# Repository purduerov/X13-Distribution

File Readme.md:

# Readme for X13-Distribution

Whenever you make a new part, download the datasheet and save it here _**and**_ with the part in the parts library

Always pull other people's changes before beginning to work
`git pull`

Be sure to push your changes after  working on them. Run:
1. `git add .` to add any files in this directory or a subdirectory
or `git add -u` to add any modified files
2. (Optional) `git clean -nX` to see what ignored files can be removed
	`git clean -fX` removes ignored files (Eagle backups)
3. `git commit -m "helpful commit message"` with a description of the work that you did
4. `git push` to push your work to github

Other helpful commands
* `git status` says information about modified and staged files
* `git log` shows the recent commits of the repository
* `git log filename.extension` show the recent commits for just that file
* `git checkout first-couple-letter-of-commit-id` lets you go back to a previous version
* `git checkout master` brings you back to the latest commit
* `git tag` lists the tags
* `git tag -a orderX -m "the version of the board placed for the X'th order"` tag a specific commit
* `git push --tags` needed to push tags to remote
* `git show orderX` show the commit log for the given tag
* `git checkout orderX` go back and interact with the files at the tagged commit

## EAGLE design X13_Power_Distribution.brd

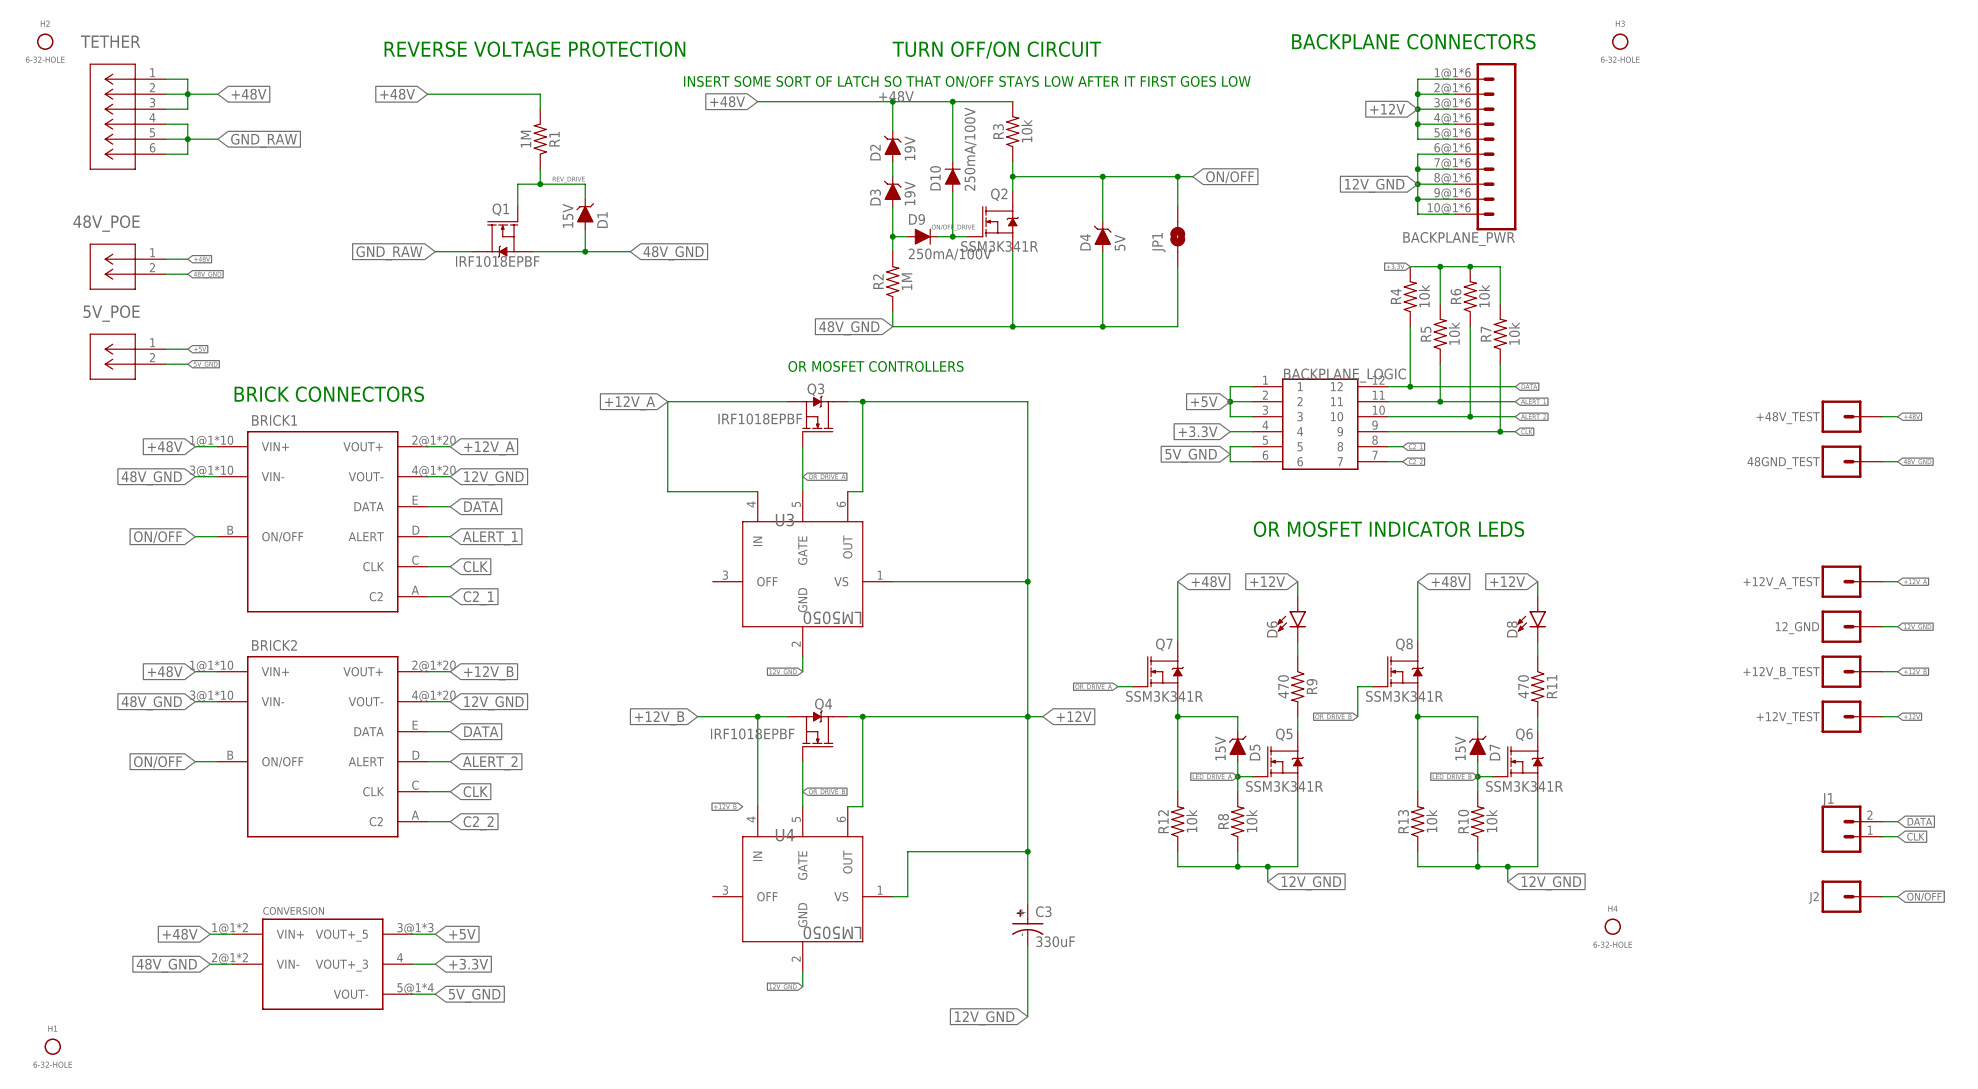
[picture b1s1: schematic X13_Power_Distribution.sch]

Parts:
5V_POE, 48V_POE: POE_TERMINAL; CONN2_282834-2_TEC
12_GND, 48GND_TEST: CONN_01; 1X01
+12V_A_TEST, +12V_B_TEST, +12V_TEST, +48V_TEST: CONN_01; 1X01
BACKPLANE_LOGIC: IPL1-106-01-L-D-K
BACKPLANE_PWR: MPPT-10-01-01-L-RA-SD
BRICK1, BRICK2: DIST2BRICKVER_D2; DIST2BRICK_D2
C3: 330uF; CAPAE1030X1050N
CONVERSION: DIST2CON
D1, D5, D7: 15V; SOD-323
D2, D3: 19V; SOD-323
D4: 5V; SOD-323
D6, D8: LED0603; LED-0603
D9, D10: 250mA/100V; SOD-323
H1, H2, H3, H4: 6-32-HOLE
J1: CONN_02; 1X02
J2: CONN_01; 1X01
JP1: JUMPER-SMT_2_NO_SILK; SMT-JUMPER_2_NO_SILK
Q1, Q3, Q4: IRF1018EPBF; TO263
Q2, Q5, Q6, Q7, Q8: SSM3K341R; SOT323
R1, R2: 1M; 0603
R3, R4, R5, R6, R7, R8, R10, R12, R13: 10k; 0603
R9, R11: 470; 0603
TETHER: 48V; CON6_P5MM_VER_TERM-BLK_TYC
U3, U4: LM5050; SOT-23-6

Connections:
5V_GND: 5V_POE.2, BACKPLANE_LOGIC.5, BACKPLANE_LOGIC.6, CONVERSION.5@1 (VOUT-), CONVERSION.5@2 (VOUT-), CONVERSION.5@3 (VOUT-), CONVERSION.5@4 (VOUT-)
12V_GND: 12_GND.1, BACKPLANE_PWR.6@1 (6), BACKPLANE_PWR.6@2 (6), BACKPLANE_PWR.6@3 (6), BACKPLANE_PWR.6@4 (6), BACKPLANE_PWR.6@5 (6), BACKPLANE_PWR.6@6 (6), BACKPLANE_PWR.7@1 (7), BACKPLANE_PWR.7@2 (7), BACKPLANE_PWR.7@3 (7), BACKPLANE_PWR.7@4 (7), BACKPLANE_PWR.7@5 (7), BACKPLANE_PWR.7@6 (7), BACKPLANE_PWR.8@1 (8), BACKPLANE_PWR.8@2 (8), BACKPLANE_PWR.8@3 (8), BACKPLANE_PWR.8@4 (8), BACKPLANE_PWR.8@5 (8), BACKPLANE_PWR.8@6 (8), BACKPLANE_PWR.9@1 (9), BACKPLANE_PWR.9@2 (9), BACKPLANE_PWR.9@3 (9), BACKPLANE_PWR.9@4 (9), BACKPLANE_PWR.9@5 (9), BACKPLANE_PWR.9@6 (9), BACKPLANE_PWR.10@1 (10), BACKPLANE_PWR.10@2 (10), BACKPLANE_PWR.10@3 (10), BACKPLANE_PWR.10@4 (10), BACKPLANE_PWR.10@5 (10), BACKPLANE_PWR.10@6 (10), BRICK1.4@1 (VOUT-), BRICK1.4@2 (VOUT-), BRICK1.4@3 (VOUT-), BRICK1.4@4 (VOUT-), BRICK1.4@5 (VOUT-), BRICK1.4@6 (VOUT-), BRICK1.4@7 (VOUT-), BRICK1.4@8 (VOUT-), BRICK1.4@9 (VOUT-), BRICK1.4@10 (VOUT-), BRICK1.4@11 (VOUT-), BRICK1.4@12 (VOUT-), BRICK1.4@13 (VOUT-), BRICK1.4@14 (VOUT-), BRICK1.4@15 (VOUT-), BRICK1.4@16 (VOUT-), BRICK1.4@17 (VOUT-), BRICK1.4@18 (VOUT-), BRICK1.4@19 (VOUT-), BRICK1.4@20 (VOUT-), BRICK2.4@1 (VOUT-), BRICK2.4@2 (VOUT-), BRICK2.4@3 (VOUT-), BRICK2.4@4 (VOUT-), BRICK2.4@5 (VOUT-), BRICK2.4@6 (VOUT-), BRICK2.4@7 (VOUT-), BRICK2.4@8 (VOUT-), BRICK2.4@9 (VOUT-), BRICK2.4@10 (VOUT-), BRICK2.4@11 (VOUT-), BRICK2.4@12 (VOUT-), BRICK2.4@13 (VOUT-), BRICK2.4@14 (VOUT-), BRICK2.4@15 (VOUT-), BRICK2.4@16 (VOUT-), BRICK2.4@17 (VOUT-), BRICK2.4@18 (VOUT-), BRICK2.4@19 (VOUT-), BRICK2.4@20 (VOUT-), C3.-, Q5.2 (S), Q6.2 (S), R8.1, R10.1, R12.1, R13.1, U3.2 (GND), U4.2 (GND)
48V_GND: 48GND_TEST.1, 48V_POE.2, BRICK1.3@1 (VIN-), BRICK1.3@2 (VIN-), BRICK1.3@3 (VIN-), BRICK1.3@4 (VIN-), BRICK1.3@5 (VIN-), BRICK1.3@6 (VIN-), BRICK1.3@7 (VIN-), BRICK1.3@8 (VIN-), BRICK1.3@9 (VIN-), BRICK1.3@10 (VIN-), BRICK2.3@1 (VIN-), BRICK2.3@2 (VIN-), BRICK2.3@3 (VIN-), BRICK2.3@4 (VIN-), BRICK2.3@5 (VIN-), BRICK2.3@6 (VIN-), BRICK2.3@7 (VIN-), BRICK2.3@8 (VIN-), BRICK2.3@9 (VIN-), BRICK2.3@10 (VIN-), CONVERSION.2@1 (VIN-), CONVERSION.2@2 (VIN-), D1.A, D4.A, JP1.1, Q1.2 (S), Q2.2 (S), R2.1
+3.3V: BACKPLANE_LOGIC.4, CONVERSION.4 (VOUT+_3), R4.2, R5.2, R6.2, R7.2
+5V: 5V_POE.1, BACKPLANE_LOGIC.1, BACKPLANE_LOGIC.2, BACKPLANE_LOGIC.3, CONVERSION.3@1 (VOUT+_5), CONVERSION.3@2 (VOUT+_5), CONVERSION.3@3 (VOUT+_5)
+12V: +12V_TEST.1, BACKPLANE_PWR.1@1 (1), BACKPLANE_PWR.1@2 (1), BACKPLANE_PWR.1@3 (1), BACKPLANE_PWR.1@4 (1), BACKPLANE_PWR.1@5 (1), BACKPLANE_PWR.1@6 (1), BACKPLANE_PWR.2@1 (2), BACKPLANE_PWR.2@2 (2), BACKPLANE_PWR.2@3 (2), BACKPLANE_PWR.2@4 (2), BACKPLANE_PWR.2@5 (2), BACKPLANE_PWR.2@6 (2), BACKPLANE_PWR.3@1 (3), BACKPLANE_PWR.3@2 (3), BACKPLANE_PWR.3@3 (3), BACKPLANE_PWR.3@4 (3), BACKPLANE_PWR.3@5 (3), BACKPLANE_PWR.3@6 (3), BACKPLANE_PWR.4@1 (4), BACKPLANE_PWR.4@2 (4), BACKPLANE_PWR.4@3 (4), BACKPLANE_PWR.4@4 (4), BACKPLANE_PWR.4@5 (4), BACKPLANE_PWR.4@6 (4), BACKPLANE_PWR.5@1 (5), BACKPLANE_PWR.5@2 (5), BACKPLANE_PWR.5@3 (5), BACKPLANE_PWR.5@4 (5), BACKPLANE_PWR.5@5 (5), BACKPLANE_PWR.5@6 (5), C3.+, D6.A, D8.A, Q3.3 (D), Q4.3 (D), U3.1 (VS), U3.6 (OUT), U4.1 (VS), U4.6 (OUT)
+12V_A: +12V_A_TEST.1, BRICK1.2@1 (VOUT+), BRICK1.2@2 (VOUT+), BRICK1.2@3 (VOUT+), BRICK1.2@4 (VOUT+), BRICK1.2@5 (VOUT+), BRICK1.2@6 (VOUT+), BRICK1.2@7 (VOUT+), BRICK1.2@8 (VOUT+), BRICK1.2@9 (VOUT+), BRICK1.2@10 (VOUT+), BRICK1.2@11 (VOUT+), BRICK1.2@12 (VOUT+), BRICK1.2@13 (VOUT+), BRICK1.2@14 (VOUT+), BRICK1.2@15 (VOUT+), BRICK1.2@16 (VOUT+), BRICK1.2@17 (VOUT+), BRICK1.2@18 (VOUT+), BRICK1.2@19 (VOUT+), BRICK1.2@20 (VOUT+), Q3.2 (S), U3.4 (IN)
+12V_B: +12V_B_TEST.1, BRICK2.2@1 (VOUT+), BRICK2.2@2 (VOUT+), BRICK2.2@3 (VOUT+), BRICK2.2@4 (VOUT+), BRICK2.2@5 (VOUT+), BRICK2.2@6 (VOUT+), BRICK2.2@7 (VOUT+), BRICK2.2@8 (VOUT+), BRICK2.2@9 (VOUT+), BRICK2.2@10 (VOUT+), BRICK2.2@11 (VOUT+), BRICK2.2@12 (VOUT+), BRICK2.2@13 (VOUT+), BRICK2.2@14 (VOUT+), BRICK2.2@15 (VOUT+), BRICK2.2@16 (VOUT+), BRICK2.2@17 (VOUT+), BRICK2.2@18 (VOUT+), BRICK2.2@19 (VOUT+), BRICK2.2@20 (VOUT+), Q4.2 (S), U4.4 (IN)
+48V: 48V_POE.1, +48V_TEST.1, BRICK1.1@1 (VIN+), BRICK1.1@2 (VIN+), BRICK1.1@3 (VIN+), BRICK1.1@4 (VIN+), BRICK1.1@5 (VIN+), BRICK1.1@6 (VIN+), BRICK1.1@7 (VIN+), BRICK1.1@8 (VIN+), BRICK1.1@9 (VIN+), BRICK1.1@10 (VIN+), BRICK2.1@1 (VIN+), BRICK2.1@2 (VIN+), BRICK2.1@3 (VIN+), BRICK2.1@4 (VIN+), BRICK2.1@5 (VIN+), BRICK2.1@6 (VIN+), BRICK2.1@7 (VIN+), BRICK2.1@8 (VIN+), BRICK2.1@9 (VIN+), BRICK2.1@10 (VIN+), CONVERSION.1@1 (VIN+), CONVERSION.1@2 (VIN+), D2.C, D10.C, Q7.3 (D), Q8.3 (D), R1.2, R3.2, TETHER.1, TETHER.2, TETHER.3
ALERT_1: BACKPLANE_LOGIC.11, BRICK1.D (ALERT), R5.1
ALERT_2: BACKPLANE_LOGIC.10, BRICK2.D (ALERT), R6.1
C2_1: BACKPLANE_LOGIC.8, BRICK1.A (C2)
C2_2: BACKPLANE_LOGIC.7, BRICK2.A (C2)
CLK: BACKPLANE_LOGIC.9, BRICK1.C (CLK), BRICK2.C (CLK), J1.1, R7.1
DATA: BACKPLANE_LOGIC.12, BRICK1.E (DATA), BRICK2.E (DATA), J1.2, R4.1
GND_RAW: Q1.3 (D), TETHER.4, TETHER.5, TETHER.6
LED_DRIVE_A: D5.A, Q5.1 (G), R8.2
LED_DRIVE_B: D7.A, Q6.1 (G), R10.2
unnamed: D2.A, D3.C
unnamed: D5.C, Q7.2 (S), R12.2
unnamed: D7.C, Q8.2 (S), R13.2
unnamed: Q5.3 (D), R9.2
unnamed: D6.C, R9.1
unnamed: Q6.3 (D), R11.2
unnamed: D8.C, R11.1
ON/OFF: BRICK1.B (ON/OFF), BRICK2.B (ON/OFF), D4.C, J2.1, JP1.2, Q2.3 (D), R3.1
ON/OFF_DRIVE: D9.C, D10.A, Q2.1 (G)
ON_DETECT: D3.A, D9.A, R2.2
OR_DRIVE_A: Q3.1 (G), Q7.1 (G), U3.5 (GATE)
OR_DRIVE_B: Q4.1 (G), Q8.1 (G), U4.5 (GATE)
REV_DRIVE: D1.C, Q1.1 (G), R1.1

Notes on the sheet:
TURN OFF/ON CIRCUIT
REVERSE VOLTAGE PROTECTION
OR MOSFET CONTROLLERS
OR MOSFET INDICATOR LEDS
BACKPLANE CONNECTORS
BRICK CONNECTORS
INSERT SOME SORT OF LATCH SO THAT ON/OFF STAYS LOW AFTER IT FIRST GOES LOW

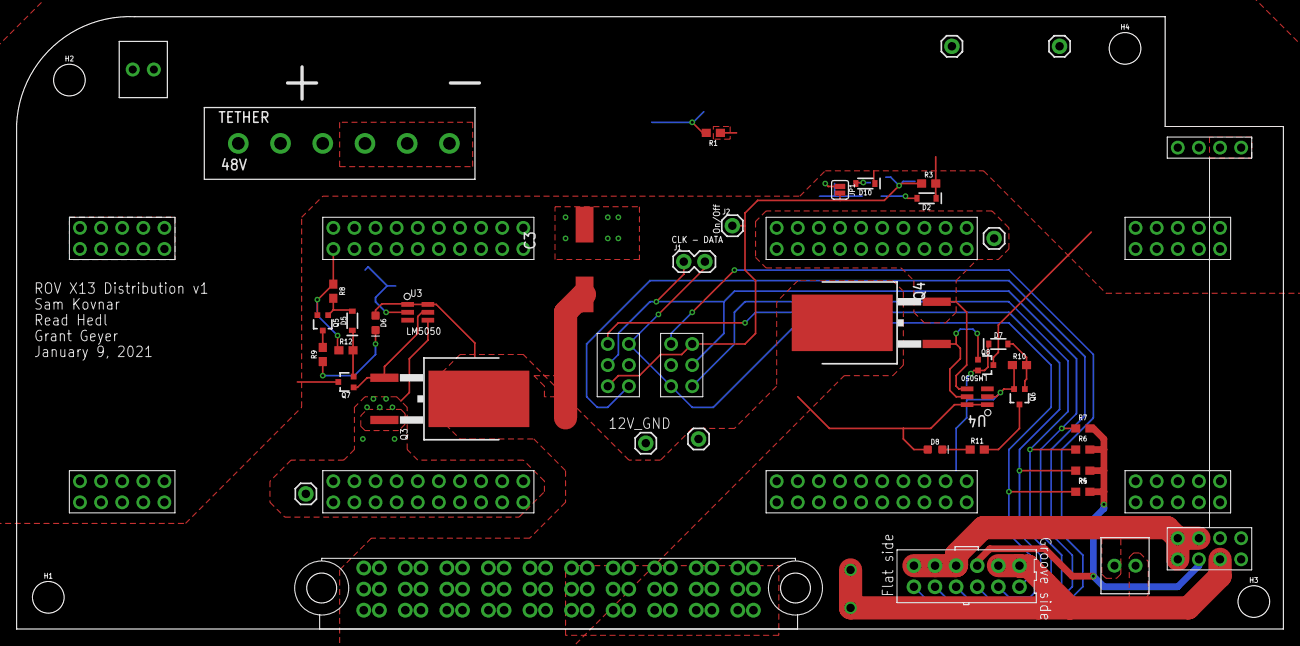
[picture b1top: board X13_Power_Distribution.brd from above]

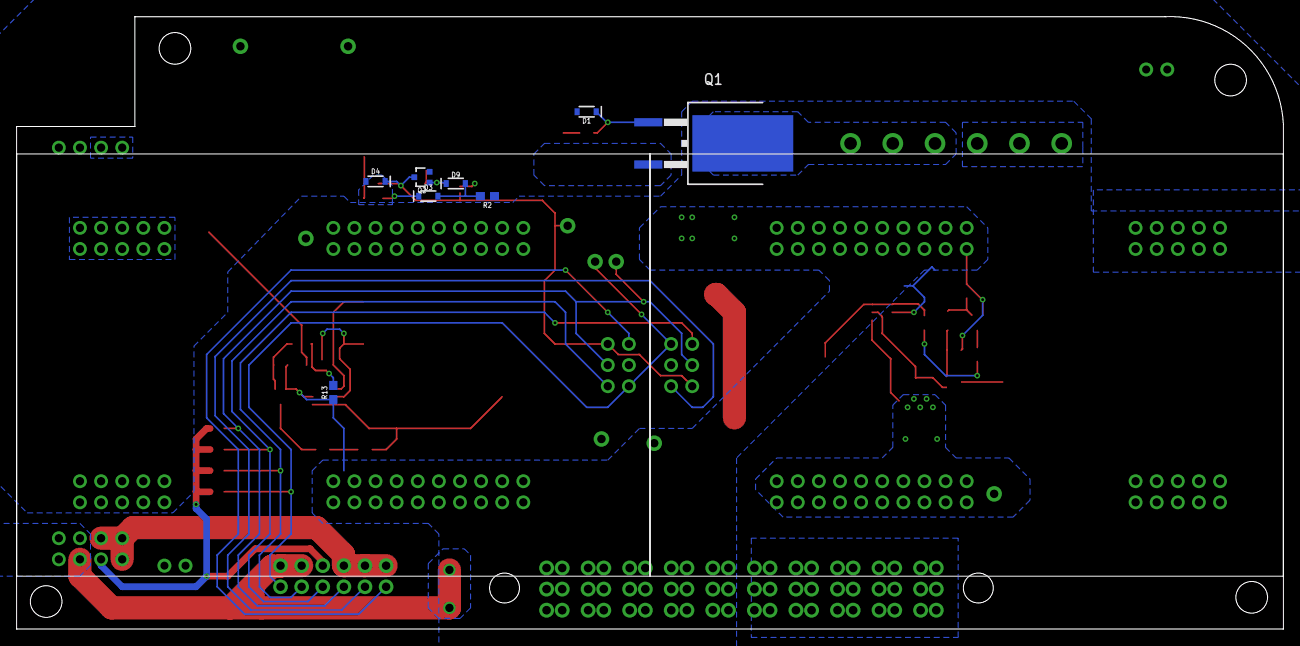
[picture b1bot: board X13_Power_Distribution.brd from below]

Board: 2 copper layers, 152.4 x 73.7 mm, 55 parts (8 on the bottom side), 31 nets.

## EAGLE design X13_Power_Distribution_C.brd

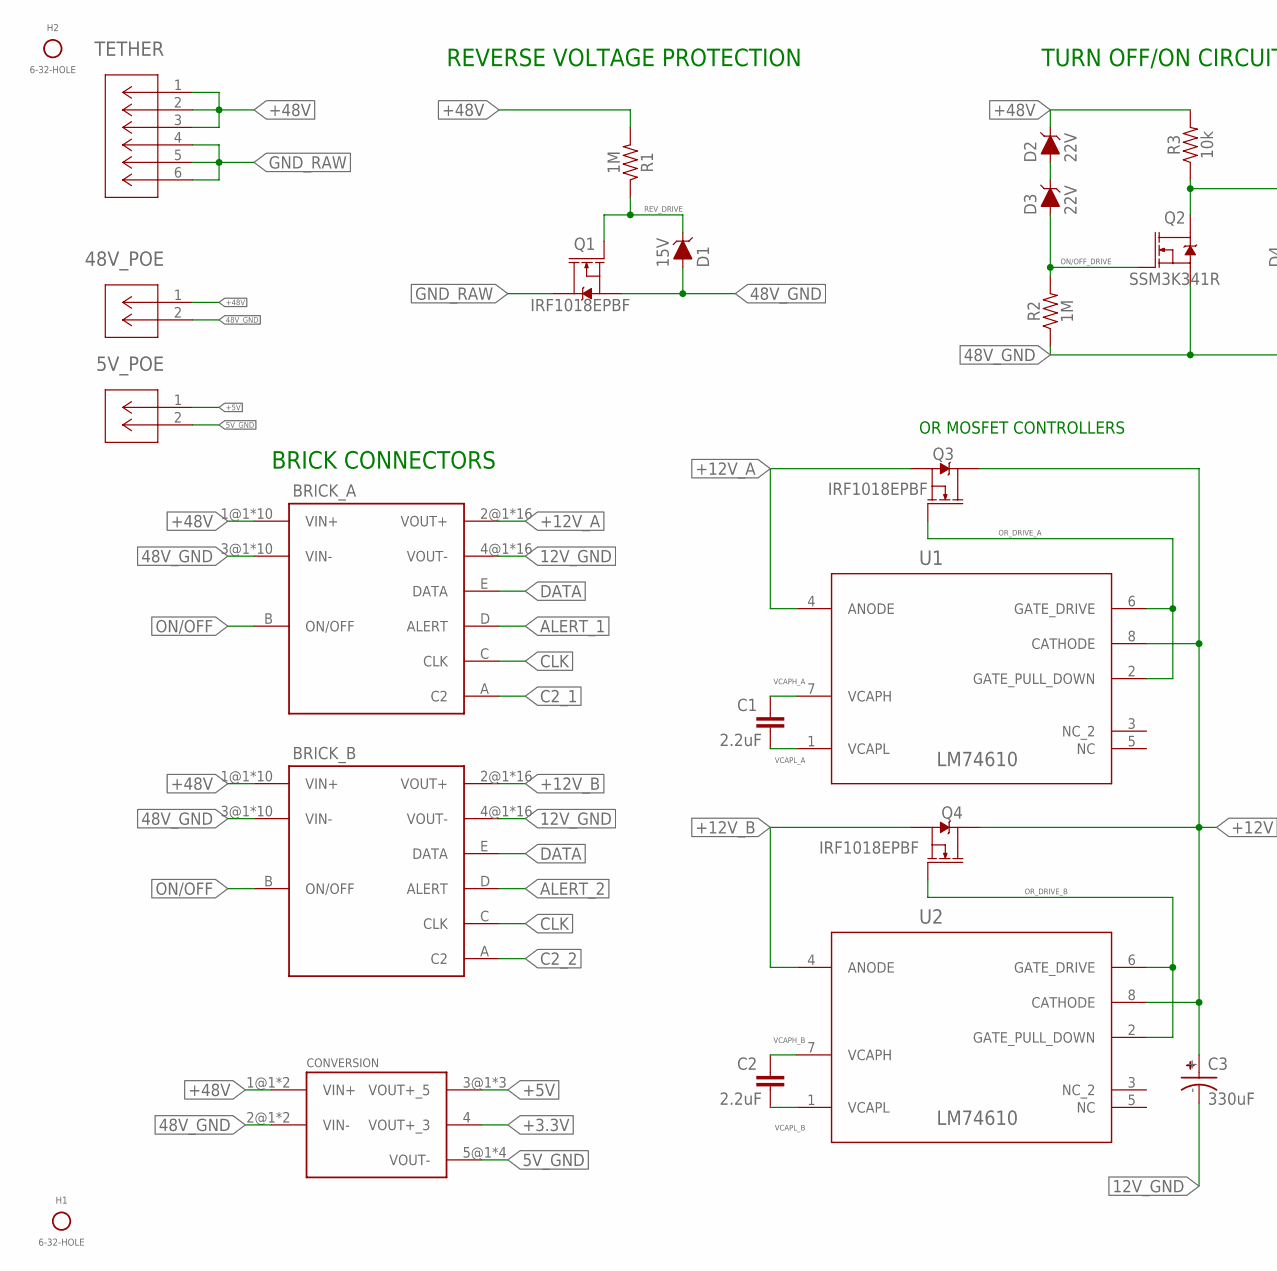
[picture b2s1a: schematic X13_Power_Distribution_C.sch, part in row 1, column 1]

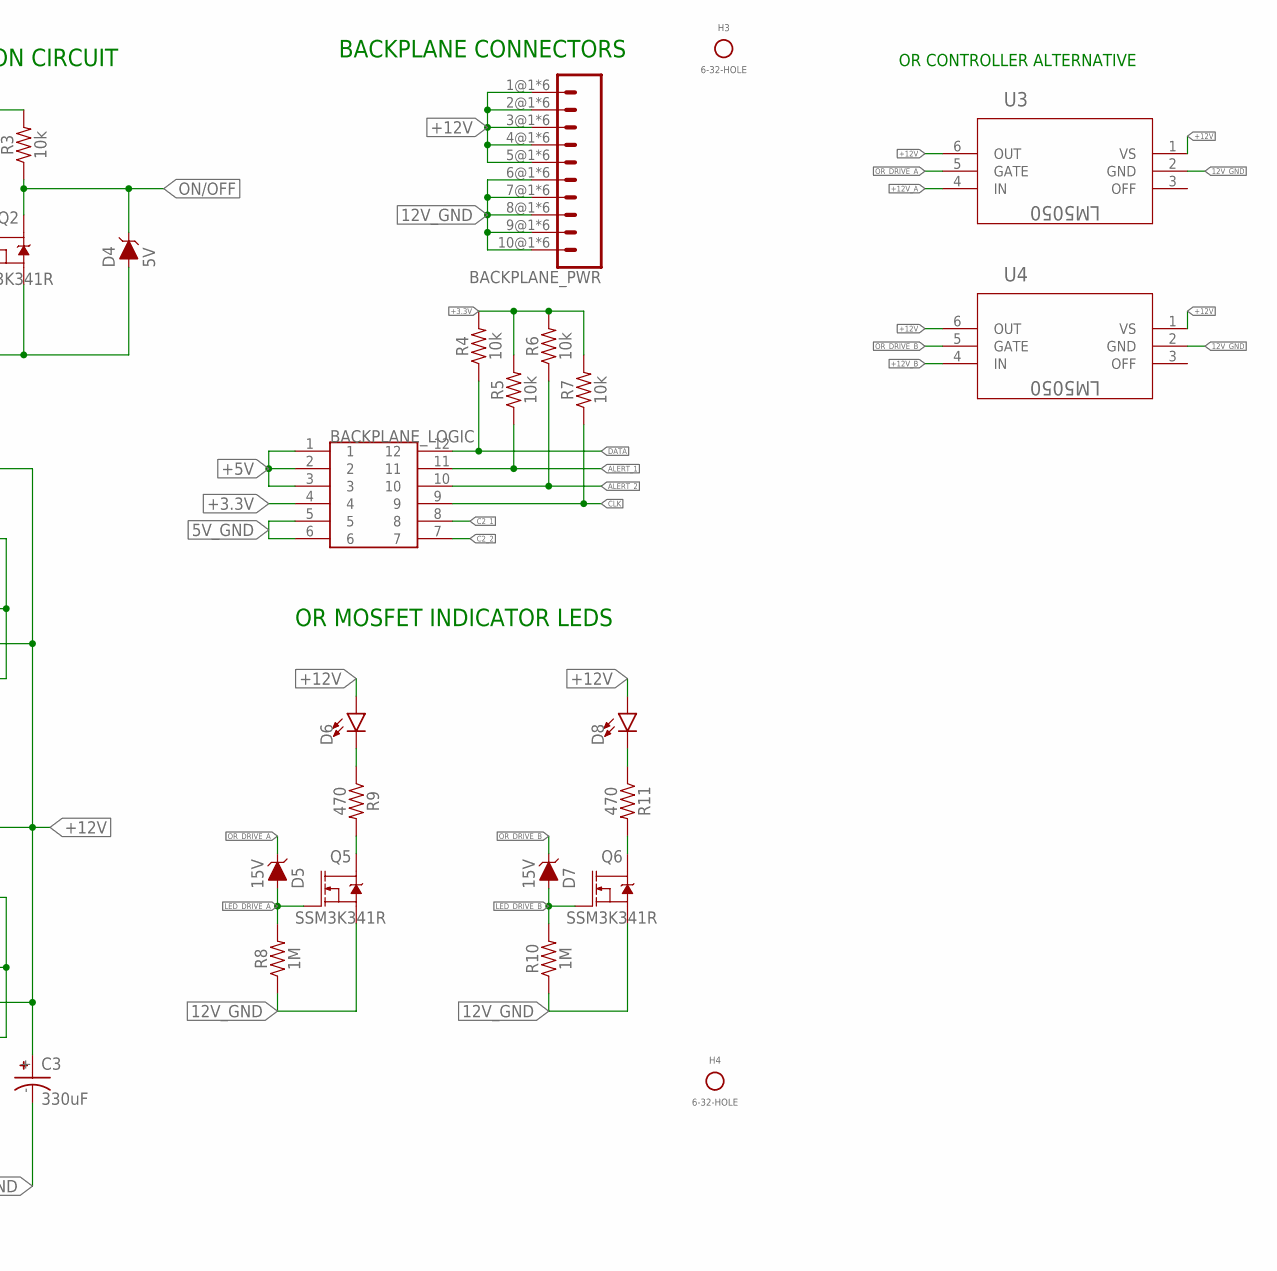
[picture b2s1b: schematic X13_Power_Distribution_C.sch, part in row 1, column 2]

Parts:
5V_POE, 48V_POE: POE_TERMINAL; CONN2_282834-2_TEC
BACKPLANE_LOGIC: IPL1-106-01-L-D-RE1-K
BACKPLANE_PWR: MPPT-10-01-01-L-RA-SD
BRICK_A: DIST2BRICK_C
BRICK_B: DIST2BRICK_C
C1, C2: 2.2uF; 0603
C3: 330uF; CAPAE1030X1050N
CONVERSION: DIST2CON
D1, D5, D7: 15V; SOD-323
D2, D3: 22V; SOD-323
D4: 5V; SOD-323
D6, D8: LED0603; LED-0603
H1, H2, H3, H4: 6-32-HOLE
Q1, Q3, Q4: IRF1018EPBF; TO263
Q2, Q5, Q6: SSM3K341R; SOT323
R1, R2, R8, R10: 1M; 0603
R3, R4, R5, R6, R7: 10k; 0603
R9, R11: 470; 0603
TETHER: 48V; CON6_P5MM_VER_TERM-BLK_TYC
U1, U2: LM74610; DGK0008A_M
U3, U4: LM5050; MK06A-M

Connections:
5V_GND: 5V_POE.2, BACKPLANE_LOGIC.5, BACKPLANE_LOGIC.6, CONVERSION.5@1 (VOUT-), CONVERSION.5@2 (VOUT-), CONVERSION.5@3 (VOUT-), CONVERSION.5@4 (VOUT-)
12V_GND: BACKPLANE_PWR.6@1 (6), BACKPLANE_PWR.6@2 (6), BACKPLANE_PWR.6@3 (6), BACKPLANE_PWR.6@4 (6), BACKPLANE_PWR.6@5 (6), BACKPLANE_PWR.6@6 (6), BACKPLANE_PWR.7@1 (7), BACKPLANE_PWR.7@2 (7), BACKPLANE_PWR.7@3 (7), BACKPLANE_PWR.7@4 (7), BACKPLANE_PWR.7@5 (7), BACKPLANE_PWR.7@6 (7), BACKPLANE_PWR.8@1 (8), BACKPLANE_PWR.8@2 (8), BACKPLANE_PWR.8@3 (8), BACKPLANE_PWR.8@4 (8), BACKPLANE_PWR.8@5 (8), BACKPLANE_PWR.8@6 (8), BACKPLANE_PWR.9@1 (9), BACKPLANE_PWR.9@2 (9), BACKPLANE_PWR.9@3 (9), BACKPLANE_PWR.9@4 (9), BACKPLANE_PWR.9@5 (9), BACKPLANE_PWR.9@6 (9), BACKPLANE_PWR.10@1 (10), BACKPLANE_PWR.10@2 (10), BACKPLANE_PWR.10@3 (10), BACKPLANE_PWR.10@4 (10), BACKPLANE_PWR.10@5 (10), BACKPLANE_PWR.10@6 (10), BRICK_A.4@1 (VOUT-), BRICK_A.4@2 (VOUT-), BRICK_A.4@3 (VOUT-), BRICK_A.4@4 (VOUT-), BRICK_A.4@5 (VOUT-), BRICK_A.4@6 (VOUT-), BRICK_A.4@7 (VOUT-), BRICK_A.4@8 (VOUT-), BRICK_A.4@9 (VOUT-), BRICK_A.4@10 (VOUT-), BRICK_A.4@11 (VOUT-), BRICK_A.4@12 (VOUT-), BRICK_A.4@13 (VOUT-), BRICK_A.4@14 (VOUT-), BRICK_A.4@15 (VOUT-), BRICK_A.4@16 (VOUT-), BRICK_B.4@1 (VOUT-), BRICK_B.4@2 (VOUT-), BRICK_B.4@3 (VOUT-), BRICK_B.4@4 (VOUT-), BRICK_B.4@5 (VOUT-), BRICK_B.4@6 (VOUT-), BRICK_B.4@7 (VOUT-), BRICK_B.4@8 (VOUT-), BRICK_B.4@9 (VOUT-), BRICK_B.4@10 (VOUT-), BRICK_B.4@11 (VOUT-), BRICK_B.4@12 (VOUT-), BRICK_B.4@13 (VOUT-), BRICK_B.4@14 (VOUT-), BRICK_B.4@15 (VOUT-), BRICK_B.4@16 (VOUT-), C3.-, Q5.2 (S), Q6.2 (S), R8.1, R10.1, U3.2 (GND), U4.2 (GND)
48V_GND: 48V_POE.2, BRICK_A.3@1 (VIN-), BRICK_A.3@2 (VIN-), BRICK_A.3@3 (VIN-), BRICK_A.3@4 (VIN-), BRICK_A.3@5 (VIN-), BRICK_A.3@6 (VIN-), BRICK_A.3@7 (VIN-), BRICK_A.3@8 (VIN-), BRICK_A.3@9 (VIN-), BRICK_A.3@10 (VIN-), BRICK_B.3@1 (VIN-), BRICK_B.3@2 (VIN-), BRICK_B.3@3 (VIN-), BRICK_B.3@4 (VIN-), BRICK_B.3@5 (VIN-), BRICK_B.3@6 (VIN-), BRICK_B.3@7 (VIN-), BRICK_B.3@8 (VIN-), BRICK_B.3@9 (VIN-), BRICK_B.3@10 (VIN-), CONVERSION.2@1 (VIN-), CONVERSION.2@2 (VIN-), D1.A, D4.A, Q1.2 (S), Q2.2 (S), R2.1
+3.3V: BACKPLANE_LOGIC.4, CONVERSION.4 (VOUT+_3), R4.2, R5.2, R6.2, R7.2
+5V: 5V_POE.1, BACKPLANE_LOGIC.1, BACKPLANE_LOGIC.2, BACKPLANE_LOGIC.3, CONVERSION.3@1 (VOUT+_5), CONVERSION.3@2 (VOUT+_5), CONVERSION.3@3 (VOUT+_5)
+12V: BACKPLANE_PWR.1@1 (1), BACKPLANE_PWR.1@2 (1), BACKPLANE_PWR.1@3 (1), BACKPLANE_PWR.1@4 (1), BACKPLANE_PWR.1@5 (1), BACKPLANE_PWR.1@6 (1), BACKPLANE_PWR.2@1 (2), BACKPLANE_PWR.2@2 (2), BACKPLANE_PWR.2@3 (2), BACKPLANE_PWR.2@4 (2), BACKPLANE_PWR.2@5 (2), BACKPLANE_PWR.2@6 (2), BACKPLANE_PWR.3@1 (3), BACKPLANE_PWR.3@2 (3), BACKPLANE_PWR.3@3 (3), BACKPLANE_PWR.3@4 (3), BACKPLANE_PWR.3@5 (3), BACKPLANE_PWR.3@6 (3), BACKPLANE_PWR.4@1 (4), BACKPLANE_PWR.4@2 (4), BACKPLANE_PWR.4@3 (4), BACKPLANE_PWR.4@4 (4), BACKPLANE_PWR.4@5 (4), BACKPLANE_PWR.4@6 (4), BACKPLANE_PWR.5@1 (5), BACKPLANE_PWR.5@2 (5), BACKPLANE_PWR.5@3 (5), BACKPLANE_PWR.5@4 (5), BACKPLANE_PWR.5@5 (5), BACKPLANE_PWR.5@6 (5), C3.+, D6.A, D8.A, Q3.3 (D), Q4.3 (D), U1.8 (CATHODE), U2.8 (CATHODE), U3.1 (VS), U3.6 (OUT), U4.1 (VS), U4.6 (OUT)
+12V_A: BRICK_A.2@1 (VOUT+), BRICK_A.2@2 (VOUT+), BRICK_A.2@3 (VOUT+), BRICK_A.2@4 (VOUT+), BRICK_A.2@5 (VOUT+), BRICK_A.2@6 (VOUT+), BRICK_A.2@7 (VOUT+), BRICK_A.2@8 (VOUT+), BRICK_A.2@9 (VOUT+), BRICK_A.2@10 (VOUT+), BRICK_A.2@11 (VOUT+), BRICK_A.2@12 (VOUT+), BRICK_A.2@13 (VOUT+), BRICK_A.2@14 (VOUT+), BRICK_A.2@15 (VOUT+), BRICK_A.2@16 (VOUT+), Q3.2 (S), U1.4 (ANODE), U3.4 (IN)
+12V_B: BRICK_B.2@1 (VOUT+), BRICK_B.2@2 (VOUT+), BRICK_B.2@3 (VOUT+), BRICK_B.2@4 (VOUT+), BRICK_B.2@5 (VOUT+), BRICK_B.2@6 (VOUT+), BRICK_B.2@7 (VOUT+), BRICK_B.2@8 (VOUT+), BRICK_B.2@9 (VOUT+), BRICK_B.2@10 (VOUT+), BRICK_B.2@11 (VOUT+), BRICK_B.2@12 (VOUT+), BRICK_B.2@13 (VOUT+), BRICK_B.2@14 (VOUT+), BRICK_B.2@15 (VOUT+), BRICK_B.2@16 (VOUT+), Q4.2 (S), U2.4 (ANODE), U4.4 (IN)
+48V: 48V_POE.1, BRICK_A.1@1 (VIN+), BRICK_A.1@2 (VIN+), BRICK_A.1@3 (VIN+), BRICK_A.1@4 (VIN+), BRICK_A.1@5 (VIN+), BRICK_A.1@6 (VIN+), BRICK_A.1@7 (VIN+), BRICK_A.1@8 (VIN+), BRICK_A.1@9 (VIN+), BRICK_A.1@10 (VIN+), BRICK_B.1@1 (VIN+), BRICK_B.1@2 (VIN+), BRICK_B.1@3 (VIN+), BRICK_B.1@4 (VIN+), BRICK_B.1@5 (VIN+), BRICK_B.1@6 (VIN+), BRICK_B.1@7 (VIN+), BRICK_B.1@8 (VIN+), BRICK_B.1@9 (VIN+), BRICK_B.1@10 (VIN+), CONVERSION.1@1 (VIN+), CONVERSION.1@2 (VIN+), D2.C, R1.2, R3.2, TETHER.1, TETHER.2, TETHER.3
ALERT_1: BACKPLANE_LOGIC.11, BRICK_A.D (ALERT), R5.1
ALERT_2: BACKPLANE_LOGIC.10, BRICK_B.D (ALERT), R6.1
C2_1: BACKPLANE_LOGIC.8, BRICK_A.A (C2)
C2_2: BACKPLANE_LOGIC.7, BRICK_B.A (C2)
CLK: BACKPLANE_LOGIC.9, BRICK_A.C (CLK), BRICK_B.C (CLK), R7.1
DATA: BACKPLANE_LOGIC.12, BRICK_A.E (DATA), BRICK_B.E (DATA), R4.1
GND_RAW: Q1.3 (D), TETHER.4, TETHER.5, TETHER.6
LED_DRIVE_A: D5.A, Q5.1 (G), R8.2
LED_DRIVE_B: D7.A, Q6.1 (G), R10.2
unnamed: D2.A, D3.C
unnamed: Q5.3 (D), R9.2
unnamed: D6.C, R9.1
unnamed: Q6.3 (D), R11.2
unnamed: D8.C, R11.1
ON/OFF: BRICK_A.B (ON/OFF), BRICK_B.B (ON/OFF), D4.C, Q2.3 (D), R3.1
ON/OFF_DRIVE: D3.A, Q2.1 (G), R2.2
OR_DRIVE_A: D5.C, Q3.1 (G), U1.2 (GATE_PULL_DOWN), U1.6 (GATE_DRIVE), U3.5 (GATE)
OR_DRIVE_B: D7.C, Q4.1 (G), U2.2 (GATE_PULL_DOWN), U2.6 (GATE_DRIVE), U4.5 (GATE)
REV_DRIVE: D1.C, Q1.1 (G), R1.1
VCAPH_A: C1.1, U1.7 (VCAPH)
VCAPH_B: C2.1, U2.7 (VCAPH)
VCAPL_A: C1.2, U1.1 (VCAPL)
VCAPL_B: C2.2, U2.1 (VCAPL)

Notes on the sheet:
TURN OFF/ON CIRCUIT
REVERSE VOLTAGE PROTECTION
OR MOSFET CONTROLLERS
OR MOSFET INDICATOR LEDS
BACKPLANE CONNECTORS
BRICK CONNECTORS
OR CONTROLLER ALTERNATIVE

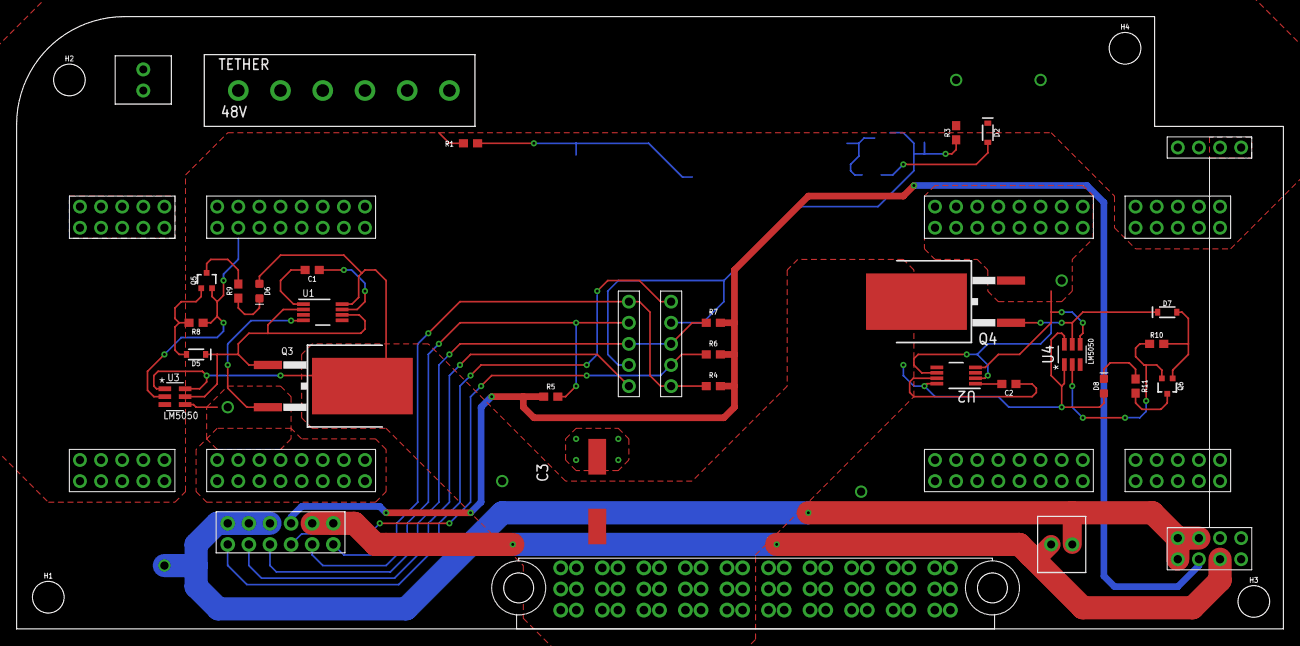
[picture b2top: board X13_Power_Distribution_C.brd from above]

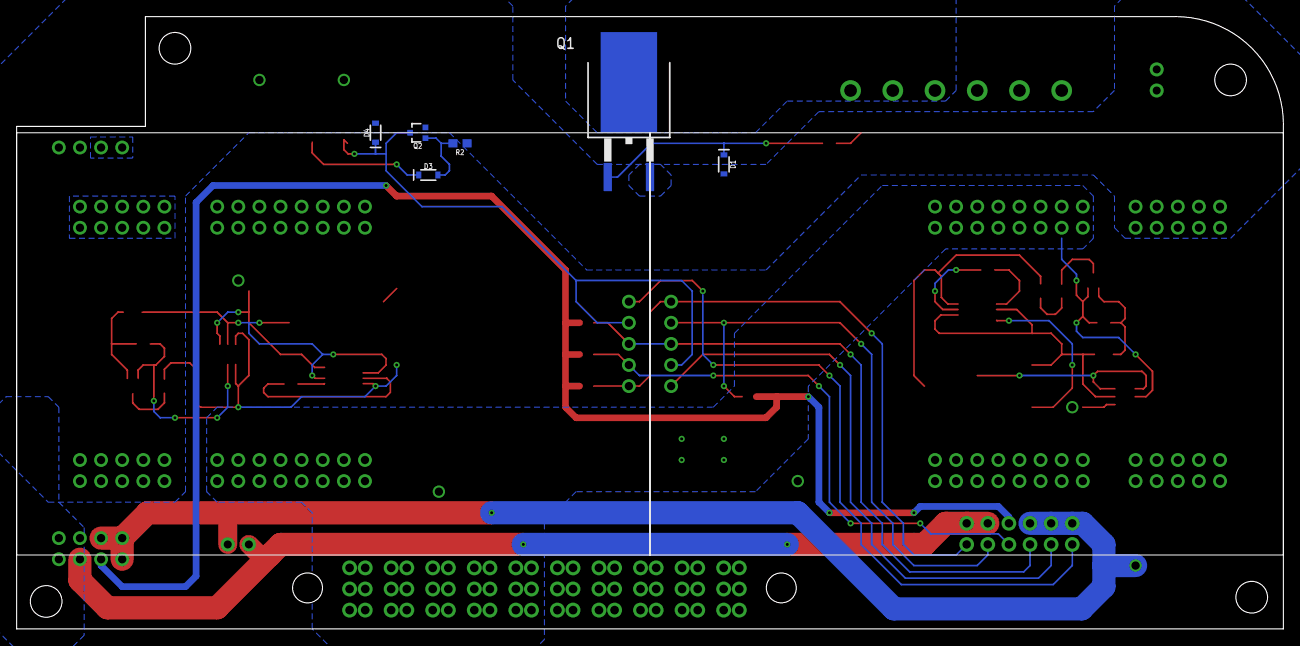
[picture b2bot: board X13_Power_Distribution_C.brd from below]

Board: 2 copper layers, 152.4 x 73.7 mm, 44 parts (6 on the bottom side), 32 nets.

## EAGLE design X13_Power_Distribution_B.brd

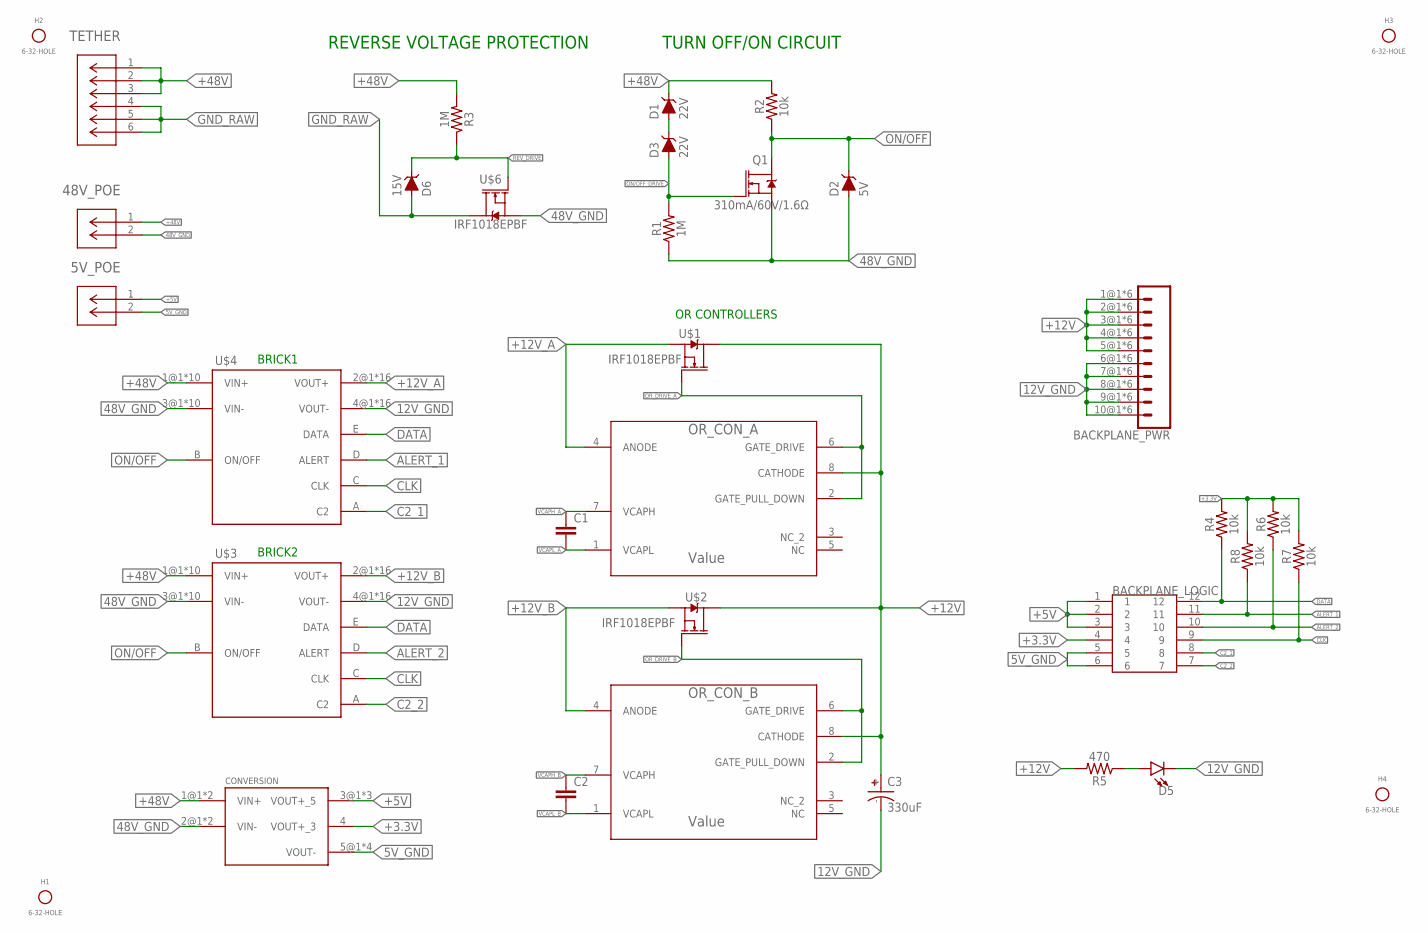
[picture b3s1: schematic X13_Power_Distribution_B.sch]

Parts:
5V_POE, 48V_POE: POE_TERMINAL; CONN2_282834-2_TEC
BACKPLANE_LOGIC: IPL1-107-01-L-D-RE-P
BACKPLANE_PWR: MPPT-10-01-01-L-RA-SD
C1, C2: 0.1UF-0603-100V-10%; 0603
C3: 330uF; CAPAE1030X1050N
CONVERSION: DIST2CON
D1, D3: 22V; SOD-323
D2: 5V; SOD-323
D5: LED0603; LED-0603
D6: 15V; SOD-323
H1, H2, H3, H4: 6-32-HOLE
OR_CON_A: Value; DGK0008A_M
OR_CON_B: Value; DGK0008A_M
Q1: 310mA/60V/1.6Ω; SOT323
R1, R3: 1M; 0603
R2, R4, R6, R7, R8: 10k; 0603
R5: 470; 0603
TETHER: 48V; CON6_P5MM_VER_TERM-BLK_TYC
U$1, U$2, U$6: IRF1018EPBF; TO263
U$3, U$4: DIST2BRICK_B

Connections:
5V_GND: 5V_POE.2, BACKPLANE_LOGIC.5, BACKPLANE_LOGIC.6, CONVERSION.5@1 (VOUT-), CONVERSION.5@2 (VOUT-), CONVERSION.5@3 (VOUT-), CONVERSION.5@4 (VOUT-)
12V_GND: BACKPLANE_PWR.6@1 (6), BACKPLANE_PWR.6@2 (6), BACKPLANE_PWR.6@3 (6), BACKPLANE_PWR.6@4 (6), BACKPLANE_PWR.6@5 (6), BACKPLANE_PWR.6@6 (6), BACKPLANE_PWR.7@1 (7), BACKPLANE_PWR.7@2 (7), BACKPLANE_PWR.7@3 (7), BACKPLANE_PWR.7@4 (7), BACKPLANE_PWR.7@5 (7), BACKPLANE_PWR.7@6 (7), BACKPLANE_PWR.8@1 (8), BACKPLANE_PWR.8@2 (8), BACKPLANE_PWR.8@3 (8), BACKPLANE_PWR.8@4 (8), BACKPLANE_PWR.8@5 (8), BACKPLANE_PWR.8@6 (8), BACKPLANE_PWR.9@1 (9), BACKPLANE_PWR.9@2 (9), BACKPLANE_PWR.9@3 (9), BACKPLANE_PWR.9@4 (9), BACKPLANE_PWR.9@5 (9), BACKPLANE_PWR.9@6 (9), BACKPLANE_PWR.10@1 (10), BACKPLANE_PWR.10@2 (10), BACKPLANE_PWR.10@3 (10), BACKPLANE_PWR.10@4 (10), BACKPLANE_PWR.10@5 (10), BACKPLANE_PWR.10@6 (10), C3.-, D5.C, U$3.4@1 (VOUT-), U$3.4@2 (VOUT-), U$3.4@3 (VOUT-), U$3.4@4 (VOUT-), U$3.4@5 (VOUT-), U$3.4@6 (VOUT-), U$3.4@7 (VOUT-), U$3.4@8 (VOUT-), U$3.4@9 (VOUT-), U$3.4@10 (VOUT-), U$3.4@11 (VOUT-), U$3.4@12 (VOUT-), U$3.4@13 (VOUT-), U$3.4@14 (VOUT-), U$3.4@15 (VOUT-), U$3.4@16 (VOUT-), U$4.4@1 (VOUT-), U$4.4@2 (VOUT-), U$4.4@3 (VOUT-), U$4.4@4 (VOUT-), U$4.4@5 (VOUT-), U$4.4@6 (VOUT-), U$4.4@7 (VOUT-), U$4.4@8 (VOUT-), U$4.4@9 (VOUT-), U$4.4@10 (VOUT-), U$4.4@11 (VOUT-), U$4.4@12 (VOUT-), U$4.4@13 (VOUT-), U$4.4@14 (VOUT-), U$4.4@15 (VOUT-), U$4.4@16 (VOUT-)
48V_GND: 48V_POE.2, CONVERSION.2@1 (VIN-), CONVERSION.2@2 (VIN-), D2.A, Q1.2 (S), R1.1, U$3.3@1 (VIN-), U$3.3@2 (VIN-), U$3.3@3 (VIN-), U$3.3@4 (VIN-), U$3.3@5 (VIN-), U$3.3@6 (VIN-), U$3.3@7 (VIN-), U$3.3@8 (VIN-), U$3.3@9 (VIN-), U$3.3@10 (VIN-), U$4.3@1 (VIN-), U$4.3@2 (VIN-), U$4.3@3 (VIN-), U$4.3@4 (VIN-), U$4.3@5 (VIN-), U$4.3@6 (VIN-), U$4.3@7 (VIN-), U$4.3@8 (VIN-), U$4.3@9 (VIN-), U$4.3@10 (VIN-), U$6.2 (S)
+3.3V: BACKPLANE_LOGIC.4, CONVERSION.4 (VOUT+_3), R4.2, R6.2, R7.2, R8.2
+5V: 5V_POE.1, BACKPLANE_LOGIC.1, BACKPLANE_LOGIC.2, BACKPLANE_LOGIC.3, CONVERSION.3@1 (VOUT+_5), CONVERSION.3@2 (VOUT+_5), CONVERSION.3@3 (VOUT+_5)
+12V: BACKPLANE_PWR.1@1 (1), BACKPLANE_PWR.1@2 (1), BACKPLANE_PWR.1@3 (1), BACKPLANE_PWR.1@4 (1), BACKPLANE_PWR.1@5 (1), BACKPLANE_PWR.1@6 (1), BACKPLANE_PWR.2@1 (2), BACKPLANE_PWR.2@2 (2), BACKPLANE_PWR.2@3 (2), BACKPLANE_PWR.2@4 (2), BACKPLANE_PWR.2@5 (2), BACKPLANE_PWR.2@6 (2), BACKPLANE_PWR.3@1 (3), BACKPLANE_PWR.3@2 (3), BACKPLANE_PWR.3@3 (3), BACKPLANE_PWR.3@4 (3), BACKPLANE_PWR.3@5 (3), BACKPLANE_PWR.3@6 (3), BACKPLANE_PWR.4@1 (4), BACKPLANE_PWR.4@2 (4), BACKPLANE_PWR.4@3 (4), BACKPLANE_PWR.4@4 (4), BACKPLANE_PWR.4@5 (4), BACKPLANE_PWR.4@6 (4), BACKPLANE_PWR.5@1 (5), BACKPLANE_PWR.5@2 (5), BACKPLANE_PWR.5@3 (5), BACKPLANE_PWR.5@4 (5), BACKPLANE_PWR.5@5 (5), BACKPLANE_PWR.5@6 (5), C3.+, OR_CON_A.8 (CATHODE), OR_CON_B.8 (CATHODE), R5.2, U$1.3 (D), U$2.3 (D)
+12V_A: OR_CON_A.4 (ANODE), U$1.2 (S), U$4.2@1 (VOUT+), U$4.2@2 (VOUT+), U$4.2@3 (VOUT+), U$4.2@4 (VOUT+), U$4.2@5 (VOUT+), U$4.2@6 (VOUT+), U$4.2@7 (VOUT+), U$4.2@8 (VOUT+), U$4.2@9 (VOUT+), U$4.2@10 (VOUT+), U$4.2@11 (VOUT+), U$4.2@12 (VOUT+), U$4.2@13 (VOUT+), U$4.2@14 (VOUT+), U$4.2@15 (VOUT+), U$4.2@16 (VOUT+)
+12V_B: OR_CON_B.4 (ANODE), U$2.2 (S), U$3.2@1 (VOUT+), U$3.2@2 (VOUT+), U$3.2@3 (VOUT+), U$3.2@4 (VOUT+), U$3.2@5 (VOUT+), U$3.2@6 (VOUT+), U$3.2@7 (VOUT+), U$3.2@8 (VOUT+), U$3.2@9 (VOUT+), U$3.2@10 (VOUT+), U$3.2@11 (VOUT+), U$3.2@12 (VOUT+), U$3.2@13 (VOUT+), U$3.2@14 (VOUT+), U$3.2@15 (VOUT+), U$3.2@16 (VOUT+)
+48V: 48V_POE.1, CONVERSION.1@1 (VIN+), CONVERSION.1@2 (VIN+), D1.C, R2.2, R3.2, TETHER.1, TETHER.2, TETHER.3, U$3.1@1 (VIN+), U$3.1@2 (VIN+), U$3.1@3 (VIN+), U$3.1@4 (VIN+), U$3.1@5 (VIN+), U$3.1@6 (VIN+), U$3.1@7 (VIN+), U$3.1@8 (VIN+), U$3.1@9 (VIN+), U$3.1@10 (VIN+), U$4.1@1 (VIN+), U$4.1@2 (VIN+), U$4.1@3 (VIN+), U$4.1@4 (VIN+), U$4.1@5 (VIN+), U$4.1@6 (VIN+), U$4.1@7 (VIN+), U$4.1@8 (VIN+), U$4.1@9 (VIN+), U$4.1@10 (VIN+)
ALERT_1: BACKPLANE_LOGIC.11, R8.1, U$4.D (ALERT)
ALERT_2: BACKPLANE_LOGIC.10, R6.1, U$3.D (ALERT)
C2_1: BACKPLANE_LOGIC.8, U$4.A (C2)
C2_2: BACKPLANE_LOGIC.7, U$3.A (C2)
CLK: BACKPLANE_LOGIC.9, R7.1, U$3.C (CLK), U$4.C (CLK)
DATA: BACKPLANE_LOGIC.12, R4.1, U$3.E (DATA), U$4.E (DATA)
GND_RAW: D6.A, TETHER.4, TETHER.5, TETHER.6, U$6.3 (D)
unnamed: D1.A, D3.C
unnamed: D5.A, R5.1
ON/OFF: D2.C, Q1.3 (D), R2.1, U$3.B (ON/OFF), U$4.B (ON/OFF)
ON/OFF_DRIVE: D3.A, Q1.1 (G), R1.2
OR_DRIVE_A: OR_CON_A.2 (GATE_PULL_DOWN), OR_CON_A.6 (GATE_DRIVE), U$1.1 (G)
OR_DRIVE_B: OR_CON_B.2 (GATE_PULL_DOWN), OR_CON_B.6 (GATE_DRIVE), U$2.1 (G)
REV_DRIVE: D6.C, R3.1, U$6.1 (G)
VCAPH_A: C1.1, OR_CON_A.7 (VCAPH)
VCAPH_B: C2.1, OR_CON_B.7 (VCAPH)
VCAPL_A: C1.2, OR_CON_A.1 (VCAPL)
VCAPL_B: C2.2, OR_CON_B.1 (VCAPL)

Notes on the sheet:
TURN OFF/ON CIRCUIT
REVERSE VOLTAGE PROTECTION
BRICK2
BRICK1
OR CONTROLLERS

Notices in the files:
parts and their libraries:
SparkFun-Capacitors: Licensing: Creative Commons ShareAlike 4.0 International - https://creativecommons.org/licenses/by-sa/4.0
COPYRIGHT: Copyright (C) 2016 Accelerated Designs. All rights reserved
